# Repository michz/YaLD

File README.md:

YaLD - Yet another LED driver
=============================

32 channel PWM driver, controlled by a AVR microcontroller,
controllable by DMX or IR remote.

DMX data port
-------------
The RJ45 connector for DMX data follows the ANSI E1.27-2 standard:
1: DMX+
2: DMX-
3: n.c.
4: n.c.
5: n.c.
6: n.c.
7: GND
8: GND

(This port *is not* compatible to Traxon/e:cue DMX interfaces.)

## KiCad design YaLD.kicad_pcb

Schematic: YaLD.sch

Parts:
C1, C2: 22p; SMD-0805
C3: 4µ7; c_elec_4x5.7
D1: grün; LED-3MM
D2: rot; LED-3MM
IC1: ATMEGA32-A; TQFP-44
IC2, IC3: PCA9685; TSSOP-28_4.4x9.7mm_Pitch0.65mm
K1: IR_RCV; Pin_Header_Straight_1x03
R1, R2: 1k5; R_0805_HandSoldering
R3: 100; R_0805_HandSoldering
R4, R5: 1k8; R_0805_HandSoldering
SW1: DIPS_10; DIP-20__300_ELL
U1: 75LBC176; SOIC-8-W
X1: 16MHz; Crystal_HC49-SD_SMD

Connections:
DEBUG_TXD: IC1.22 ((TMS)PC3); also elsewhere on the board
DIP1: IC1.30 ((ADC7)PA7), SW1.11
DIP2: IC1.31 ((ADC6)PA6), SW1.12
DIP3: IC1.32 ((ADC5)PA5), SW1.13
DIP4: IC1.33 ((ADC4)PA4), SW1.14
DIP5: IC1.34 ((ADC3)PA3), SW1.15
DIP6: IC1.35 ((ADC2)PA2), SW1.16
DIP7: IC1.36 ((ADC1)PA1), SW1.17
DIP8: IC1.37 ((ADC0)PA0), SW1.18
DIP9: IC1.40 ((T0/XCK)PB0), SW1.19
DIP10: IC1.41 ((T1)PB1), SW1.20
DMXminus: U1.7 (BUS-); also elsewhere on the board
DMXplus: U1.6 (BUS+); also elsewhere on the board
GND: C1.1, C2.1, C3.2, IC1.6 (GND), IC1.14 ((OC1A)PD5), IC1.18 (GND), IC1.28 (GND), IC1.39 (GND), IC2.1 (A0), IC2.2 (A1), IC2.3 (A2), IC2.4 (A3), IC2.14 (V_SS), IC2.23 (-OE), IC2.24 (A5), IC2.25 (EXTCLK), IC3.1 (A0), IC3.2 (A1), IC3.3 (A2), IC3.14 (V_SS), IC3.23 (-OE), IC3.24 (A5), IC3.25 (EXTCLK), K1.1, SW1.1, SW1.2, SW1.3, SW1.4, SW1.5, SW1.6, SW1.7, SW1.8, SW1.9, SW1.10, U1.5 (GND); also elsewhere on the board
INT0: IC1.11 ((INT0)PD2), U1.2 (/RE), U1.3 (DE)
LEDgreen: D1.2, IC1.42 ((AIN0/INT2)PB2)
LEDred: D2.2, IC1.43 ((AIN1/OC0)PB3)
MISO: IC1.2 ((MISO)PB6); also elsewhere on the board
MOSI: IC1.1 ((MOSI)PB5); also elsewhere on the board
unnamed: C1.2, IC1.7 (XTAL2), X1.1
unnamed: C2.2, IC1.8 (XTAL1), X1.2
unnamed: D1.1, R1.2
unnamed: D2.1, R2.2
PWM0: IC2.6 (LED0); also elsewhere on the board
PWM1: IC2.7 (LED1); also elsewhere on the board
PWM2: IC2.8 (LED2); also elsewhere on the board
PWM3: IC2.9 (LED3); also elsewhere on the board
PWM4: IC2.10 (LED4); also elsewhere on the board
PWM5: IC2.11 (LED5); also elsewhere on the board
PWM6: IC2.12 (LED6); also elsewhere on the board
PWM7: IC2.13 (LED7); also elsewhere on the board
PWM8: IC2.15 (LED8); also elsewhere on the board
PWM9: IC2.16 (LED9); also elsewhere on the board
PWM10: IC2.17 (LED10); also elsewhere on the board
PWM11: IC2.18 (LED11); also elsewhere on the board
PWM12: IC2.19 (LED12); also elsewhere on the board
PWM13: IC2.20 (LED13); also elsewhere on the board
PWM14: IC2.21 (LED14); also elsewhere on the board
PWM15: IC2.22 (LED15); also elsewhere on the board
PWM16: IC3.6 (LED0); also elsewhere on the board
PWM17: IC3.7 (LED1); also elsewhere on the board
PWM18: IC3.8 (LED2); also elsewhere on the board
PWM19: IC3.9 (LED3); also elsewhere on the board
PWM20: IC3.10 (LED4); also elsewhere on the board
PWM21: IC3.11 (LED5); also elsewhere on the board
PWM22: IC3.12 (LED6); also elsewhere on the board
PWM23: IC3.13 (LED7); also elsewhere on the board
PWM24: IC3.15 (LED8); also elsewhere on the board
PWM25: IC3.16 (LED9); also elsewhere on the board
PWM26: IC3.17 (LED10); also elsewhere on the board
PWM27: IC3.18 (LED11); also elsewhere on the board
PWM28: IC3.19 (LED12); also elsewhere on the board
PWM29: IC3.20 (LED13); also elsewhere on the board
PWM30: IC3.21 (LED14); also elsewhere on the board
PWM31: IC3.22 (LED15); also elsewhere on the board
RESET: IC1.4 (~RESET); also elsewhere on the board
RXD: IC1.9 ((RXD)PD0), U1.1 (ROUT); also elsewhere on the board
SCK: IC1.3 ((SCK)PB7); also elsewhere on the board
SCL: IC1.19 ((SCL)PC0), IC2.26 (SCL), IC3.26 (SCL), R5.2
SDA: IC1.20 ((SDA)PC1), IC2.27 (SDA), IC3.27 (SDA), R4.2
TXD: IC1.10 ((TXD)PD1), U1.4 (DIN); also elsewhere on the board
VCC: IC1.5 (VCC), IC1.17 (VCC), IC1.27 (AVCC), IC1.38 (VCC), IC2.5 (A4), IC2.28 (V_DD), IC3.4 (A3), IC3.5 (A4), IC3.28 (V_DD), R1.1, R2.1, R3.2, R4.1, R5.1, U1.8 (VCC); also elsewhere on the board

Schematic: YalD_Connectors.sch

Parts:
C4: 330n; SMD-1206
C5: 100n; SMD-0805
C6: 100n; SMD-1206
J1: RJDMXin; RJ45_8
J2: RJDMXout; RJ45_8
K2: DMXin; Pin_Header_Straight_1x03
K3: DMXout; Pin_Header_Straight_1x03
P1: PWR_IN; Pin_Header_Straight_1x02
P2: ISP; Pin_Header_Straight_2x05
P3, P14: CONN_01X02; Pin_Header_Straight_1x02
P4, P5, P6, P7, P8, P9, P10, P11, P12, P13: CONN_01X04; Pin_Header_Straight_1x04
P15: DEBUG; Pin_Header_Straight_1x02
U2: 7805_f; TO-220

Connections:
12V: C4.1, P1.2 (PM), P3.1, P3.3, P4.1, P5.1, P6.1, P7.1, P8.1, P9.1, P10.1, P11.1, P12.1, P13.1, P14.1, U2.1 (VI)
DEBUG_TXD: P15.1; also elsewhere on the board
DMXminus: J1.2, J2.2, K2.3, K3.3; also elsewhere on the board
DMXplus: J1.1, J2.1, K2.2 (PM), K3.2 (PM); also elsewhere on the board
GND: C4.2, C5.2, C6.2, J1.7, J1.8, J2.7, J2.8, K2.1, K3.1, P1.1, P2.4, P2.6, P2.8, P2.10, P15.2, U2.2 (GND); also elsewhere on the board
MISO: P2.9; also elsewhere on the board
MOSI: P2.1; also elsewhere on the board
OUT0: P3.2; also elsewhere on the board
OUT1: P4.2; also elsewhere on the board
OUT2: P4.3; also elsewhere on the board
OUT3: P4.4; also elsewhere on the board
OUT4: P5.2; also elsewhere on the board
OUT5: P5.3; also elsewhere on the board
OUT6: P5.4; also elsewhere on the board
OUT7: P8.2; also elsewhere on the board
OUT8: P13.4; also elsewhere on the board
OUT9: P6.2; also elsewhere on the board
OUT10: P6.3; also elsewhere on the board
OUT11: P6.4; also elsewhere on the board
OUT12: P7.2; also elsewhere on the board
OUT13: P7.3; also elsewhere on the board
OUT14: P7.4; also elsewhere on the board
OUT15: P3.4; also elsewhere on the board
OUT16: P8.3; also elsewhere on the board
OUT17: P8.4; also elsewhere on the board
OUT18: P9.2; also elsewhere on the board
OUT19: P9.3; also elsewhere on the board
OUT20: P9.4; also elsewhere on the board
OUT21: P10.2; also elsewhere on the board
OUT22: P10.3; also elsewhere on the board
OUT23: P10.4; also elsewhere on the board
OUT24: P11.2; also elsewhere on the board
OUT25: P11.3; also elsewhere on the board
OUT26: P11.4; also elsewhere on the board
OUT27: P12.2; also elsewhere on the board
OUT28: P12.3; also elsewhere on the board
OUT29: P12.4; also elsewhere on the board
OUT30: P13.2; also elsewhere on the board
OUT31: P13.3; also elsewhere on the board
RESET: P2.5; also elsewhere on the board
SCK: P2.7; also elsewhere on the board
VCC: C5.1, C6.1, P2.2, U2.3 (VO); also elsewhere on the board

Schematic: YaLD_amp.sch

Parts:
R6, R7, R8, R9, R10, R11, R12, R13, R14, R15, R16, R17, R18, R19, R20, R21, R22, R23, R24, R25, R26, R27, R28, R29, R30, R31, R32, R33, R34, R35, R36, R37: 100k; R_0805_HandSoldering
U3, U4, U5, U6, U7, U8, U9, U10, U11, U12, U13, U14, U15, U16, U17, U18: IRF7103; SOIC-8_3.9x4.9mm_Pitch1.27mm

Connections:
GND: R6.1, R7.1, R8.1, R9.1, R10.1, R11.1, R12.1, R13.1, R14.1, R15.1, R16.1, R17.1, R18.1, R19.1, R20.1, R21.1, R22.1, R23.1, R24.1, R25.1, R26.1, R27.1, R28.1, R29.1, R30.1, R31.1, R32.1, R33.1, R34.1, R35.1, R36.1, R37.1, U3.1 (S), U3.3 (S), U4.1 (S), U4.3 (S), U5.1 (S), U5.3 (S), U6.1 (S), U6.3 (S), U7.1 (S), U7.3 (S), U8.1 (S), U8.3 (S), U9.1 (S), U9.3 (S), U10.1 (S), U10.3 (S), U11.1 (S), U11.3 (S), U12.1 (S), U12.3 (S), U13.1 (S), U13.3 (S), U14.1 (S), U14.3 (S), U15.1 (S), U15.3 (S), U16.1 (S), U16.3 (S), U17.1 (S), U17.3 (S), U18.1 (S), U18.3 (S); also elsewhere on the board
OUT0: U3.5 (D@2); also elsewhere on the board
OUT1: U3.7 (D@2); also elsewhere on the board
OUT2: U4.5 (D@2); also elsewhere on the board
OUT3: U4.7 (D@2); also elsewhere on the board
OUT4: U5.5 (D@2); also elsewhere on the board
OUT5: U5.7 (D@2); also elsewhere on the board
OUT6: U6.5 (D@2); also elsewhere on the board
OUT7: U6.7 (D@2); also elsewhere on the board
OUT8: U7.5 (D@2); also elsewhere on the board
OUT9: U7.7 (D@2); also elsewhere on the board
OUT10: U8.5 (D@2); also elsewhere on the board
OUT11: U8.7 (D@2); also elsewhere on the board
OUT12: U9.5 (D@2); also elsewhere on the board
OUT13: U9.7 (D@2); also elsewhere on the board
OUT14: U10.5 (D@2); also elsewhere on the board
OUT15: U10.7 (D@2); also elsewhere on the board
OUT16: U11.5 (D@2); also elsewhere on the board
OUT17: U11.7 (D@2); also elsewhere on the board
OUT18: U12.5 (D@2); also elsewhere on the board
OUT19: U12.7 (D@2); also elsewhere on the board
OUT20: U13.5 (D@2); also elsewhere on the board
OUT21: U13.7 (D@2); also elsewhere on the board
OUT22: U14.5 (D@2); also elsewhere on the board
OUT23: U14.7 (D@2); also elsewhere on the board
OUT24: U15.5 (D@2); also elsewhere on the board
OUT25: U15.7 (D@2); also elsewhere on the board
OUT26: U16.5 (D@2); also elsewhere on the board
OUT27: U16.7 (D@2); also elsewhere on the board
OUT28: U17.5 (D@2); also elsewhere on the board
OUT29: U17.7 (D@2); also elsewhere on the board
OUT30: U18.5 (D@2); also elsewhere on the board
OUT31: U18.7 (D@2); also elsewhere on the board
PWM0: R6.2, U3.4 (G); also elsewhere on the board
PWM1: R7.2, U3.2 (G); also elsewhere on the board
PWM2: R8.2, U4.4 (G); also elsewhere on the board
PWM3: R9.2, U4.2 (G); also elsewhere on the board
PWM4: R10.2, U5.4 (G); also elsewhere on the board
PWM5: R11.2, U5.2 (G); also elsewhere on the board
PWM6: R12.2, U6.4 (G); also elsewhere on the board
PWM7: R13.2, U6.2 (G); also elsewhere on the board
PWM8: R14.2, U7.4 (G); also elsewhere on the board
PWM9: R15.2, U7.2 (G); also elsewhere on the board
PWM10: R16.2, U8.4 (G); also elsewhere on the board
PWM11: R17.2, U8.2 (G); also elsewhere on the board
PWM12: R18.2, U9.4 (G); also elsewhere on the board
PWM13: R19.2, U9.2 (G); also elsewhere on the board
PWM14: R20.2, U10.4 (G); also elsewhere on the board
PWM15: R21.2, U10.2 (G); also elsewhere on the board
PWM16: R22.2, U11.4 (G); also elsewhere on the board
PWM17: R23.2, U11.2 (G); also elsewhere on the board
PWM18: R24.2, U12.4 (G); also elsewhere on the board
PWM19: R25.2, U12.2 (G); also elsewhere on the board
PWM20: R26.2, U13.4 (G); also elsewhere on the board
PWM21: R27.2, U13.2 (G); also elsewhere on the board
PWM22: R28.2, U14.4 (G); also elsewhere on the board
PWM23: R29.2, U14.2 (G); also elsewhere on the board
PWM24: R30.2, U15.4 (G); also elsewhere on the board
PWM25: R31.2, U15.2 (G); also elsewhere on the board
PWM26: R32.2, U16.4 (G); also elsewhere on the board
PWM27: R33.2, U16.2 (G); also elsewhere on the board
PWM28: R34.2, U17.4 (G); also elsewhere on the board
PWM29: R35.2, U17.2 (G); also elsewhere on the board
PWM30: R36.2, U18.4 (G); also elsewhere on the board
PWM31: R37.2, U18.2 (G); also elsewhere on the board

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
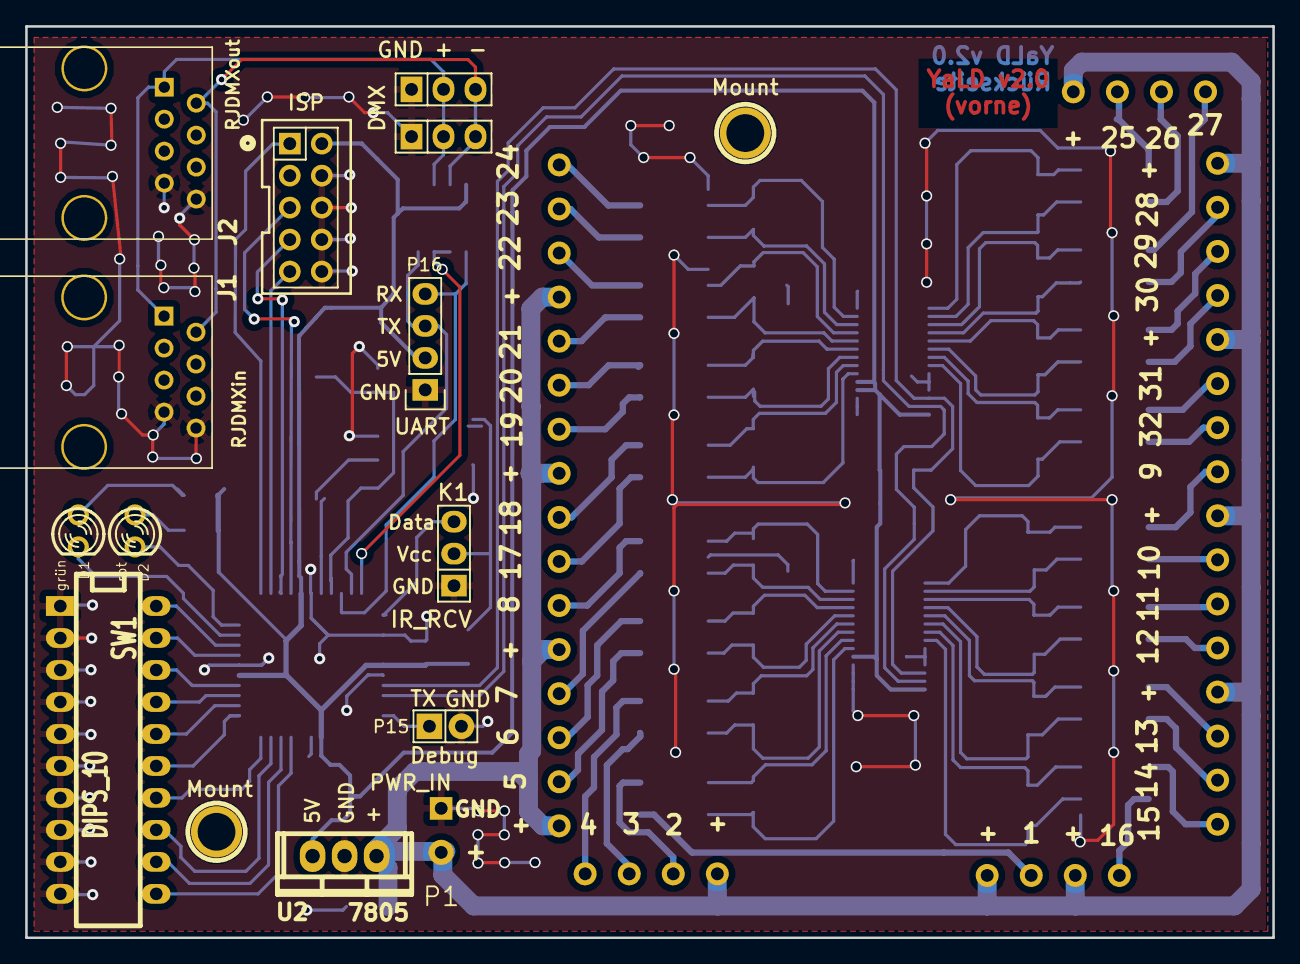
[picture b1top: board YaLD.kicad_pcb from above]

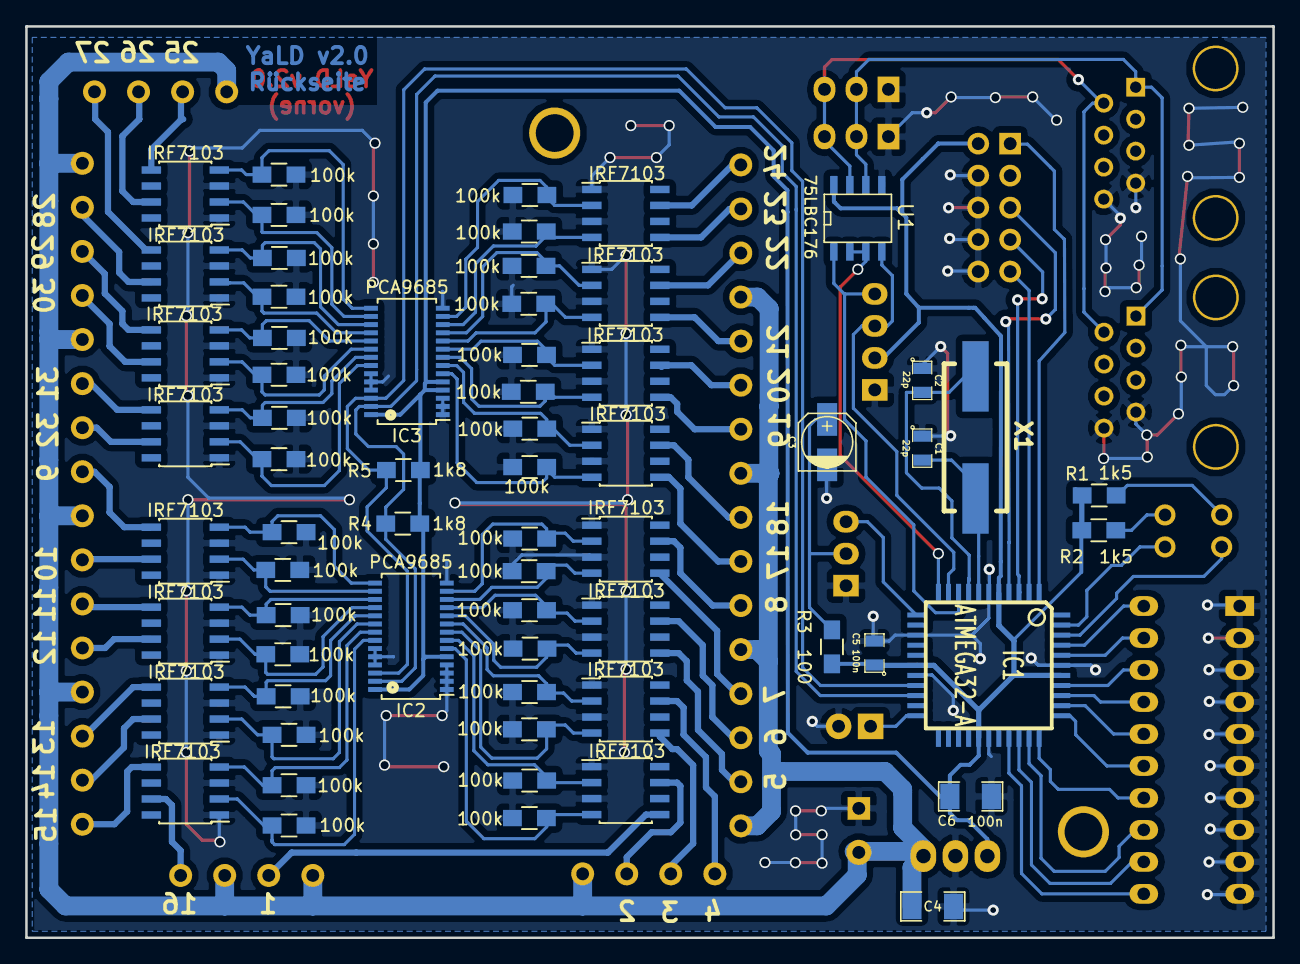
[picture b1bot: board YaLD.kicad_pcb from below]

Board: 2 copper layers, 99.1 x 72.4 mm, 90 parts (64 on the bottom side), 97 nets.

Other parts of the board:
1PIN, 1PIN#2: P***; 1pin
P16: UART; Pin_Header_Straight_1x04

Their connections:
GND: P16.1; also elsewhere on the board
RXD: P16.4; also elsewhere on the board
TXD: P16.3; also elsewhere on the board
VCC: P16.2; also elsewhere on the board

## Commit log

2014-10-26 added README
2014-10-26 initial commit, some work done, NOT ready for production!
2014-10-27 Layout somewhat like *finished*
2014-11-01 fixed RJ45 connectors + folder libs.pretty added
    RJ45 were on wrong side;
2014-11-20 refixed RJ45 - they have been on CORRECT side before!
2015-02-02 DMX plus/minus switched, GND airwire connected
    + nicer silk print (more readable)
2015-02-02 added ISP header orientation to silk
2015-02-03 added debug connector (software UART TX)
2015-07-04 meta stuff
2015-08-22 ir codes updated
2016-08-25 old output added
2016-08-25 changed outputs to 3.5mm pitch
2016-08-26 added silk texts, corrected bugs
2016-08-26 moved rj45
2016-08-26 added gerber files for YaLD v2.0
2016-08-26 changed default state of 'use gerber extensions'
2019-08-28 version from old firmware repo + beginning of README
2019-08-28 move header files into own directory
    + add gitignore to not track binaries
2020-06-27 first firmware changes to support yald as esp "sidekick"
2020-06-27 add bill of materials for some formerly unmarked parts on the board
    (just for convience to not need to open kicad to build a pcb)
2020-06-27 update gitignore
2020-06-27 simplify uart_simple algorithm
2020-06-27 add readme about simple_uart algorithm
2020-06-28 add first start for esp32 firmware
2020-06-28 add example file for wlan credentials
2020-06-28 first simple esp implementation works
2020-11-22 add some (non functional!) mqtt stuff
2022-10-16 add current working state of bridge
2022-10-16 disable debug + disable webserver for the moment
2022-10-16 esp32 bridge: initialize `data` array to be empty on start
2022-10-16 add update via http
2022-10-16 esp bridge: improve int parsing / fix bug
